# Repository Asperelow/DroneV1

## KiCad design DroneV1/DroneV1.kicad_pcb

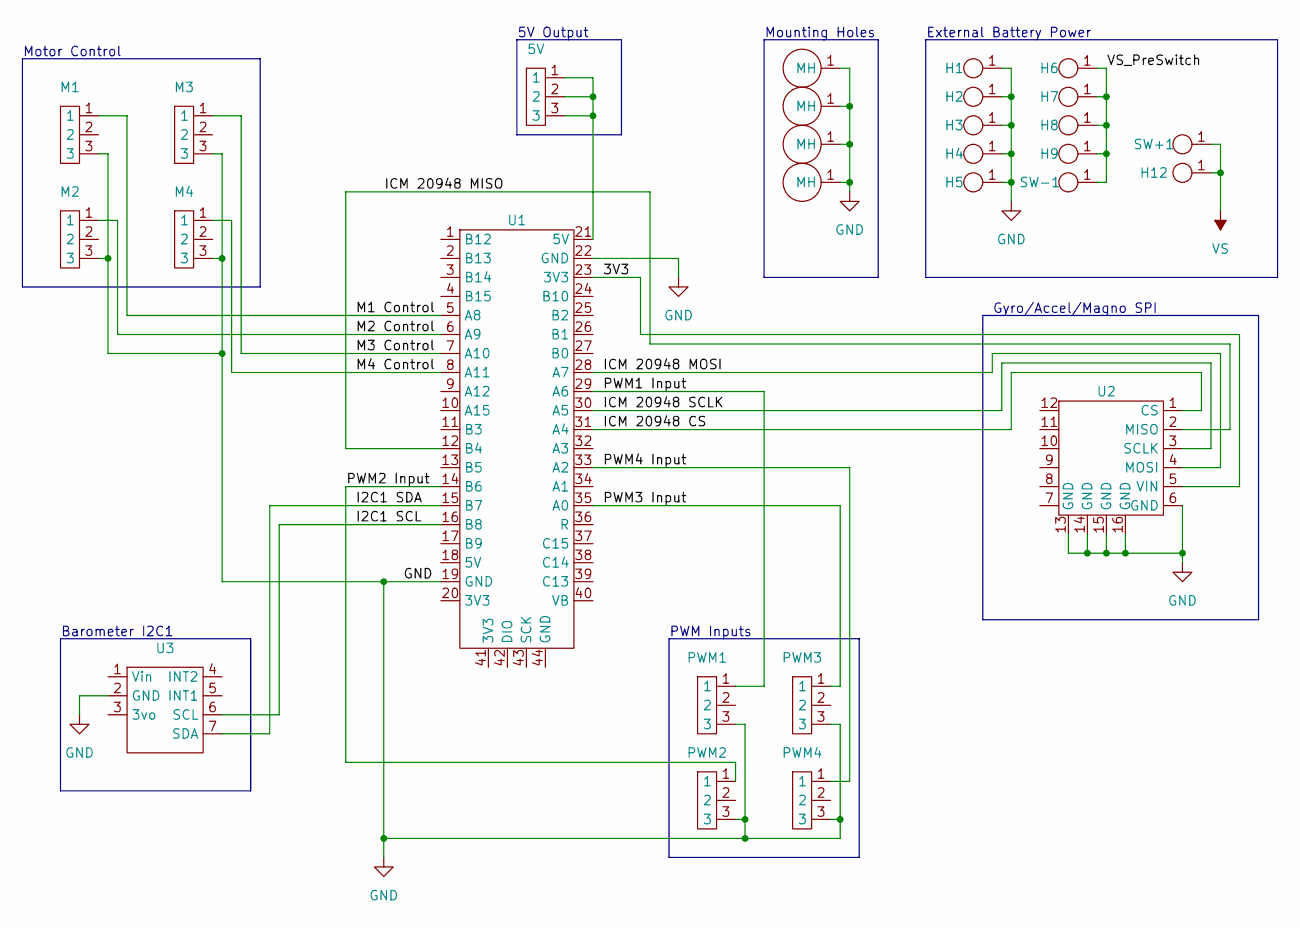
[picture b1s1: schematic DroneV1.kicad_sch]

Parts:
5V: Header3x1Spaced2.54mm
H1, H2, H3, H4, H5, H6, H7, H8, H9, H12: ESCMounting
M1, M2, M3, M4: Header3x1Spaced2.54mm
MH1, MH2, MH3, MH4: M3MountingHole
PWM1, PWM2, PWM3, PWM4: Header3x1Spaced2.54mm
SW+1: ESCMounting
SW-1: ESCMounting
U1: STM32BlackPill40Pin
U2: ICM-20948 GyrAccMag
U3: MPL3115A2_Barometer

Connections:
/3V3: U1.23 (3V3), U2.5 (VIN)
/I2C1 SCL: U1.16 (B8), U3.6 (SCL)
/I2C1 SDA: U1.15 (B7), U3.7 (SDA)
/ICM 20948 CS: U1.31 (A4), U2.1 (CS)
/ICM 20948 MISO: U1.12 (B4), U2.2 (MISO)
/ICM 20948 MOSI: U1.28 (A7), U2.4 (MOSI)
/ICM 20948 SCLK: U1.30 (A5), U2.3 (SCLK)
/M1 Control: M1.1, U1.5 (A8)
/M2 Control: M2.1, U1.6 (A9)
/M3 Control: M3.1, U1.7 (A10)
/M4 Control: M4.1, U1.8 (A11)
/PWM1 Input: PWM1.1, U1.29 (A6)
/PWM2 Input: PWM2.1, U1.14 (B6)
/PWM3 Input: PWM3.1, U1.35 (A0)
/PWM4 Input: PWM4.1, U1.33 (A2)
/VS_PreSwitch: H6.1, H7.1, H8.1, H9.1, SW-1.1
GND: H1.1, H2.1, H3.1, H4.1, H5.1, M1.3, M2.3, M3.3, M4.3, MH1.1 (MH), MH2.1 (MH), MH3.1 (MH), MH4.1 (MH), PWM1.3, PWM2.3, PWM3.3, PWM4.3, U1.19 (GND), U1.22 (GND), U2.6 (GND), U2.13 (GND), U2.14 (GND), U2.15 (GND), U2.16 (GND), U3.2 (GND)
unnamed 17: 5V.1, 5V.2, 5V.3, U1.21 (5V); also elsewhere on the board
VS: H12.1, SW+1.1

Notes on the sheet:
Barometer I2C1
Mounting Holes
Motor Control
Gyro/Accel/Magno SPI
5V Output
External Battery Power
PWM Inputs

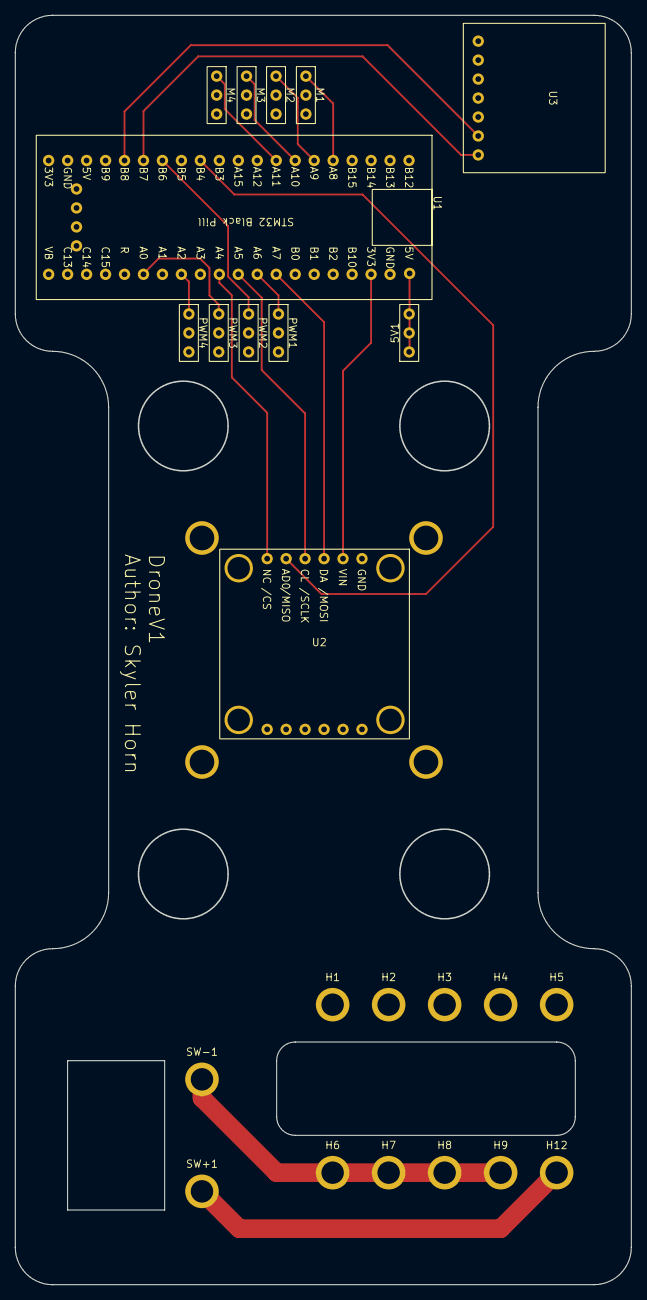
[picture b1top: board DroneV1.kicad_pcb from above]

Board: 2 copper layers, 82.4 x 169.9 mm, 28 parts (0 on the bottom side), 19 nets.

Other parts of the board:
5V1: Header3x1Spaced2.54mm

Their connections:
unnamed 17: 5V1.1, 5V1.2, 5V1.3; also elsewhere on the board

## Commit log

2024-02-03 Add files via upload
    Updated barometer collaborative filter - working, but untuned.
    Fixed ESC/motor startup calibration. Also tied user controls to motor speeds in the z-axis, **missing roll pitch and yaw**.
